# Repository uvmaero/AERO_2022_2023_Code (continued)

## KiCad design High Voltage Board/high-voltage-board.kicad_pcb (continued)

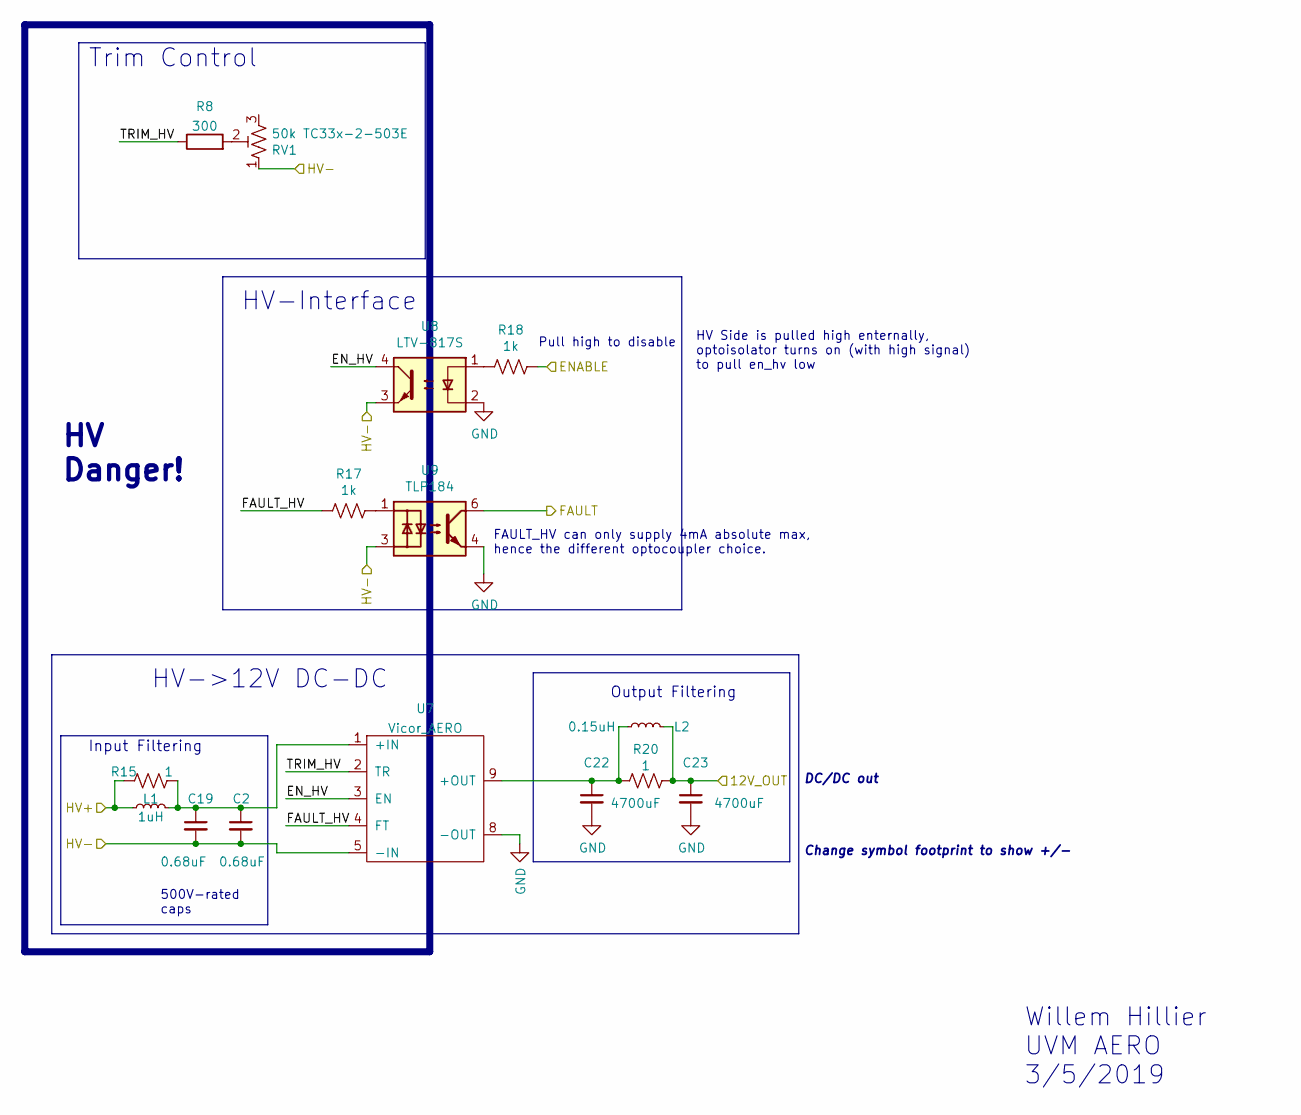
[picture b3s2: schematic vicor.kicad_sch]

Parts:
C2, C19: 0.68uF; C_Rect_L18.0mm_W8.0mm_P15.00mm_FKS3_FKP3
C22, C23: 4700uF; C_Radial_D18.0mm_H35.5mm_P7.50mm
L1: 1uH; L_1008_2520Metric_Pad1.43x2.20mm_HandSolder
L2: 0.15uH; L_0805_2012Metric_Pad1.15x1.40mm_HandSolder
R8: 300; R_0603_1608Metric_Pad0.98x0.95mm_HandSolder
R15, R20: 1; R_2512_6332Metric_Pad1.40x3.35mm_HandSolder
R17, R18: 1k; R_0603_1608Metric_Pad0.98x0.95mm_HandSolder
RV1: 50k TC33x-2-503E; Potentiometer_Bourns_TC33X_Vertical
U7: Vicor_AERO; vicor-socket-no-cutouts
U8: LTV-817S; SMDIP-4_W9.53mm_Clearance8mm
U9: TLP184; MFSOP6-4_4.4x3.6mm_P1.27mm

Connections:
/DCDC_OUT: C23.1, L2.2, R20.1; also elsewhere on the board
/DC_DC_EN: R18.1; also elsewhere on the board
/DC_DC_FAULT: U9.6; also elsewhere on the board
/vicor/EN_HV: U7.3 (EN), U8.4
/vicor/FAULT_HV: R17.2, U7.4 (FT)
/vicor/HV+: L1.1, R15.2; also elsewhere on the board
/vicor/TRIM_HV: R8.1, U7.2 (TR)
GND: C22.2, C23.2, U7.8 (-OUT), U8.2, U9.4; also elsewhere on the board
HV-: C2.2, C19.2, RV1.1, U7.5 (-IN), U8.3, U9.3; also elsewhere on the board
unnamed: C2.1, C19.1, L1.2, R15.1, U7.1 (+IN)
unnamed: C22.1, L2.1, R20.2, U7.9 (+OUT)
unnamed: R8.2, RV1.2
unnamed: R17.1, U9.1
unnamed: R18.2, U8.1

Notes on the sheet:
DC/DC out
Output Filtering
500V-rated caps
Willem Hillier UVM AERO 3/5/2019
Input Filtering
Trim Control
HV-Interface
Change symbol footprint to show +/-
Pull high to disable
HV->12V DC-DC
HV Side is pulled high enternally, optoisolator turns on (with high signal) to pull en_hv low
HV Danger!
FAULT_HV can only supply 4mA absolute max, hence the different optocoupler choice.

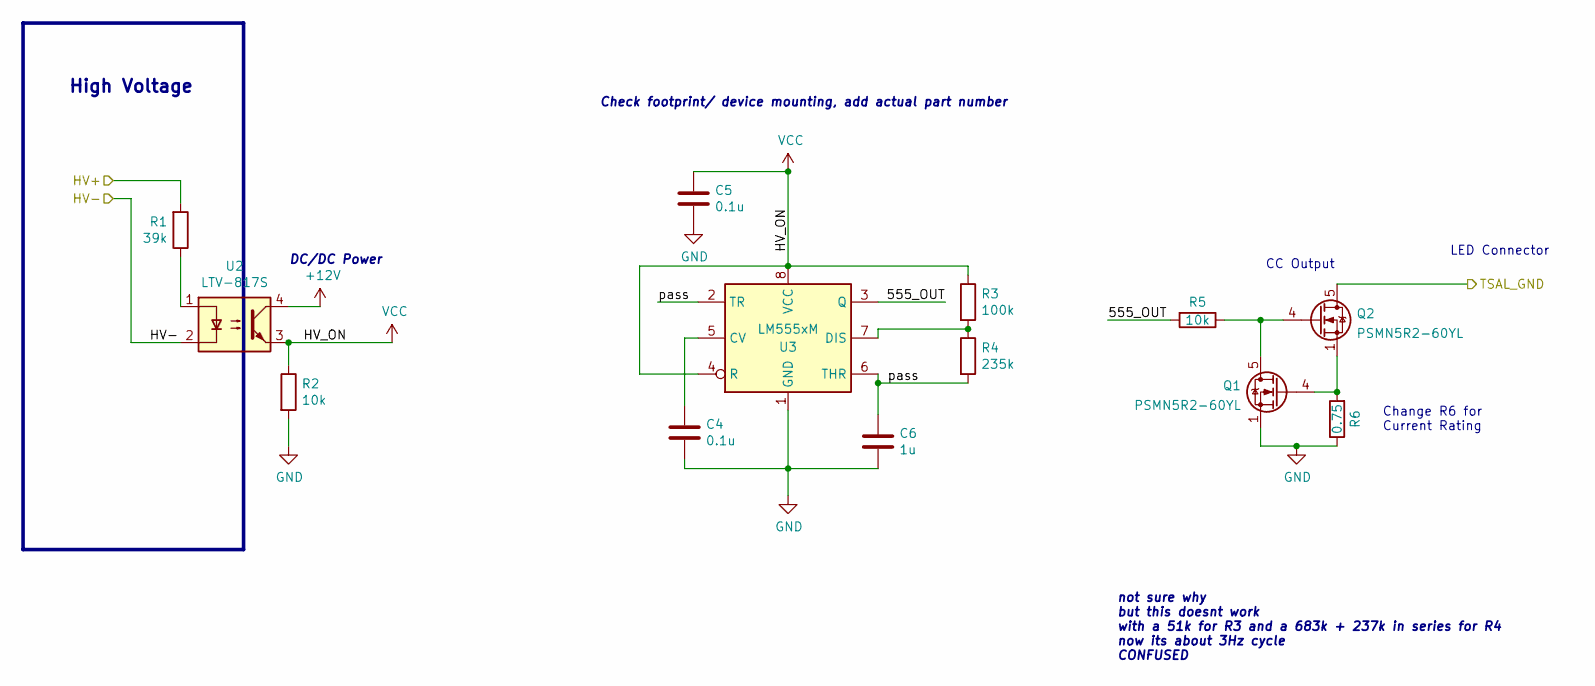
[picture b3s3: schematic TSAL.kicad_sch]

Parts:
C4, C5: 0.1u; C_0603_1608Metric_Pad1.08x0.95mm_HandSolder
C6: 1u; C_0603_1608Metric_Pad1.08x0.95mm_HandSolder
Q1, Q2: PSMN5R2-60YL; LFPAK56
R1: 39k; R_Axial_DIN0411_L9.9mm_D3.6mm_P25.40mm_Horizontal
R2, R5: 10k; R_0603_1608Metric_Pad0.98x0.95mm_HandSolder
R3: 100k; R_0603_1608Metric_Pad0.98x0.95mm_HandSolder
R4: 235k; R_0603_1608Metric_Pad0.98x0.95mm_HandSolder
R6: 0.75; R_2512_6332Metric_Pad1.40x3.35mm_HandSolder
U2: LTV-817S; SMDIP-4_W9.53mm_Clearance8mm
U3: LM555xM; SOIC-8_3.9x4.9mm_P1.27mm

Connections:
+12V: U2.4; also elsewhere on the board
/TSAL/555_OUT: R5.2, U3.3 (Q)
/TSAL/HV+: R1.2; also elsewhere on the board
/TSAL/pass: C6.1, R4.2, U3.2 (TR), U3.6 (THR)
/TSAL_GND: Q2.5 (D); also elsewhere on the board
GND: C4.2, C5.2, C6.2, Q1.1 (S), Q1.2 (S), Q1.3 (S), R2.2, R6.1, U3.1 (GND); also elsewhere on the board
HV-: U2.2; also elsewhere on the board
unnamed: C4.1, U3.5 (CV)
unnamed: Q1.4 (G), Q2.1 (S), Q2.2 (S), Q2.3 (S), R6.2
unnamed: Q1.5 (D), Q2.4 (G), R5.1
unnamed: R1.1, U2.1
unnamed: R3.2, R4.1, U3.7 (DIS)
VCC: C5.1, R2.1, R3.1, U2.3, U3.4 (R), U3.8 (VCC)

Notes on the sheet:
Check footprint/ device mounting, add actual part number
DC/DC Power
Change R6 for Current Rating
CC Output
LED Connector
High Voltage
not sure why but this doesnt work with a 51k for R3 and a 683k + 237k in series for R4 now its about 3Hz cycle CONFUSED

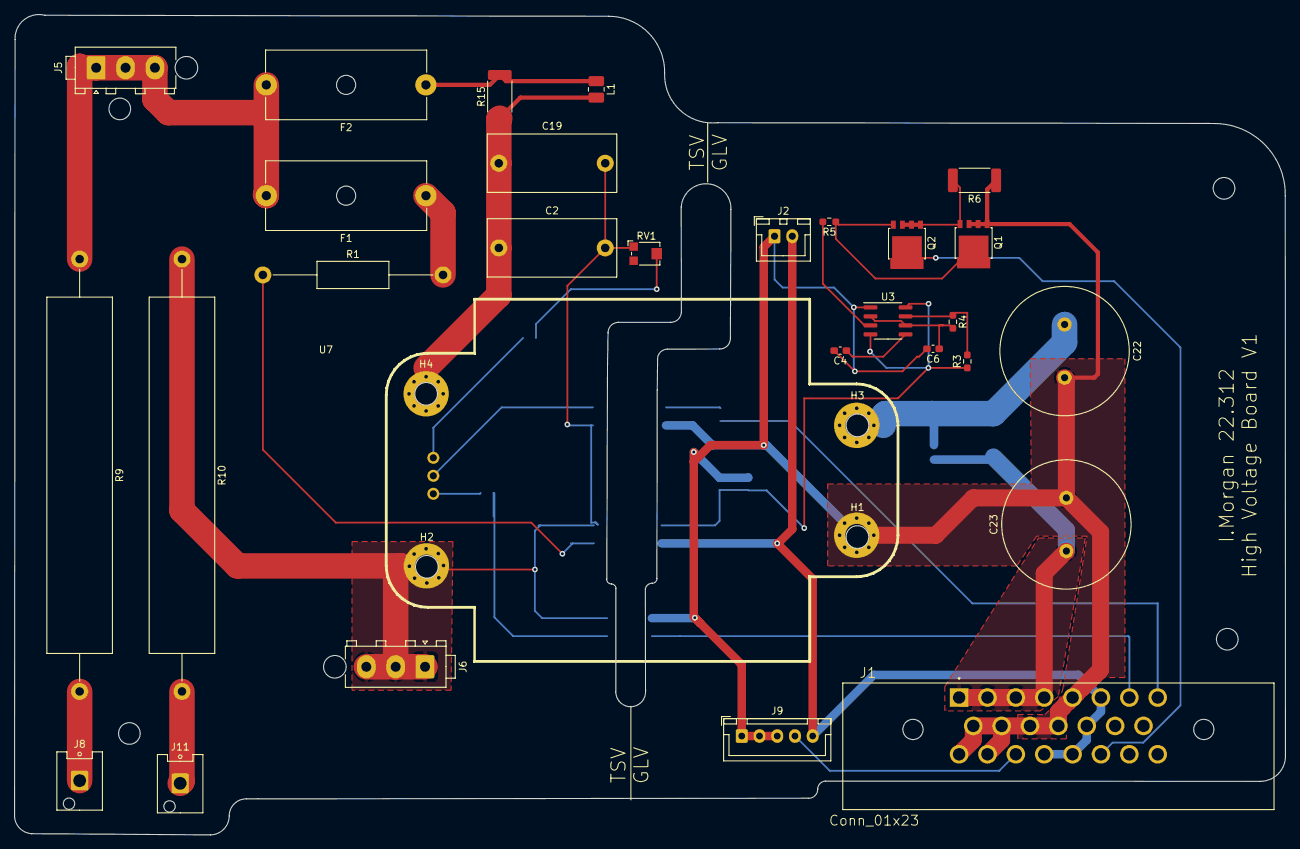
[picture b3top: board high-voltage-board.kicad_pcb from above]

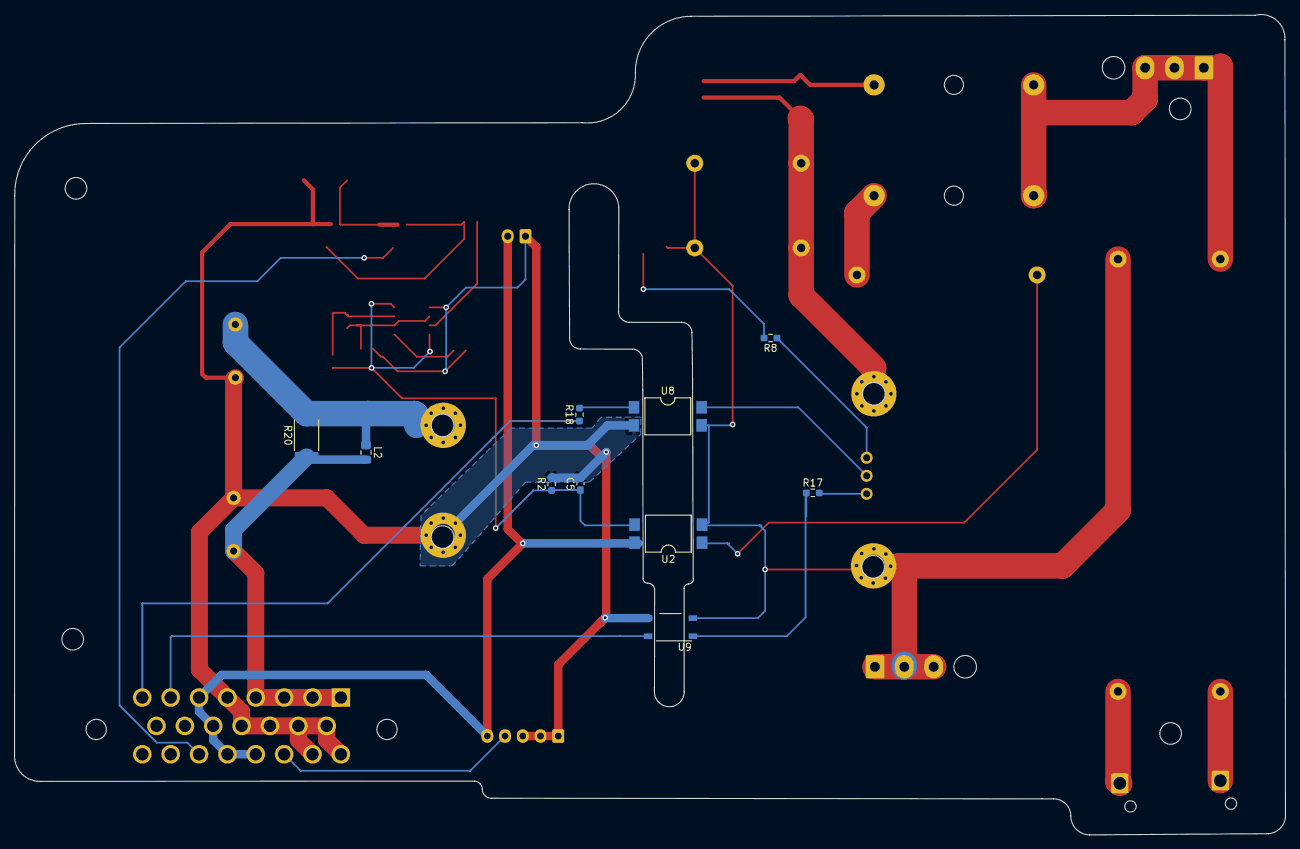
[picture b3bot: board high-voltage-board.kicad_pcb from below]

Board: 2 copper layers, 179.2 x 115.7 mm, 43 parts (10 on the bottom side), 29 nets.

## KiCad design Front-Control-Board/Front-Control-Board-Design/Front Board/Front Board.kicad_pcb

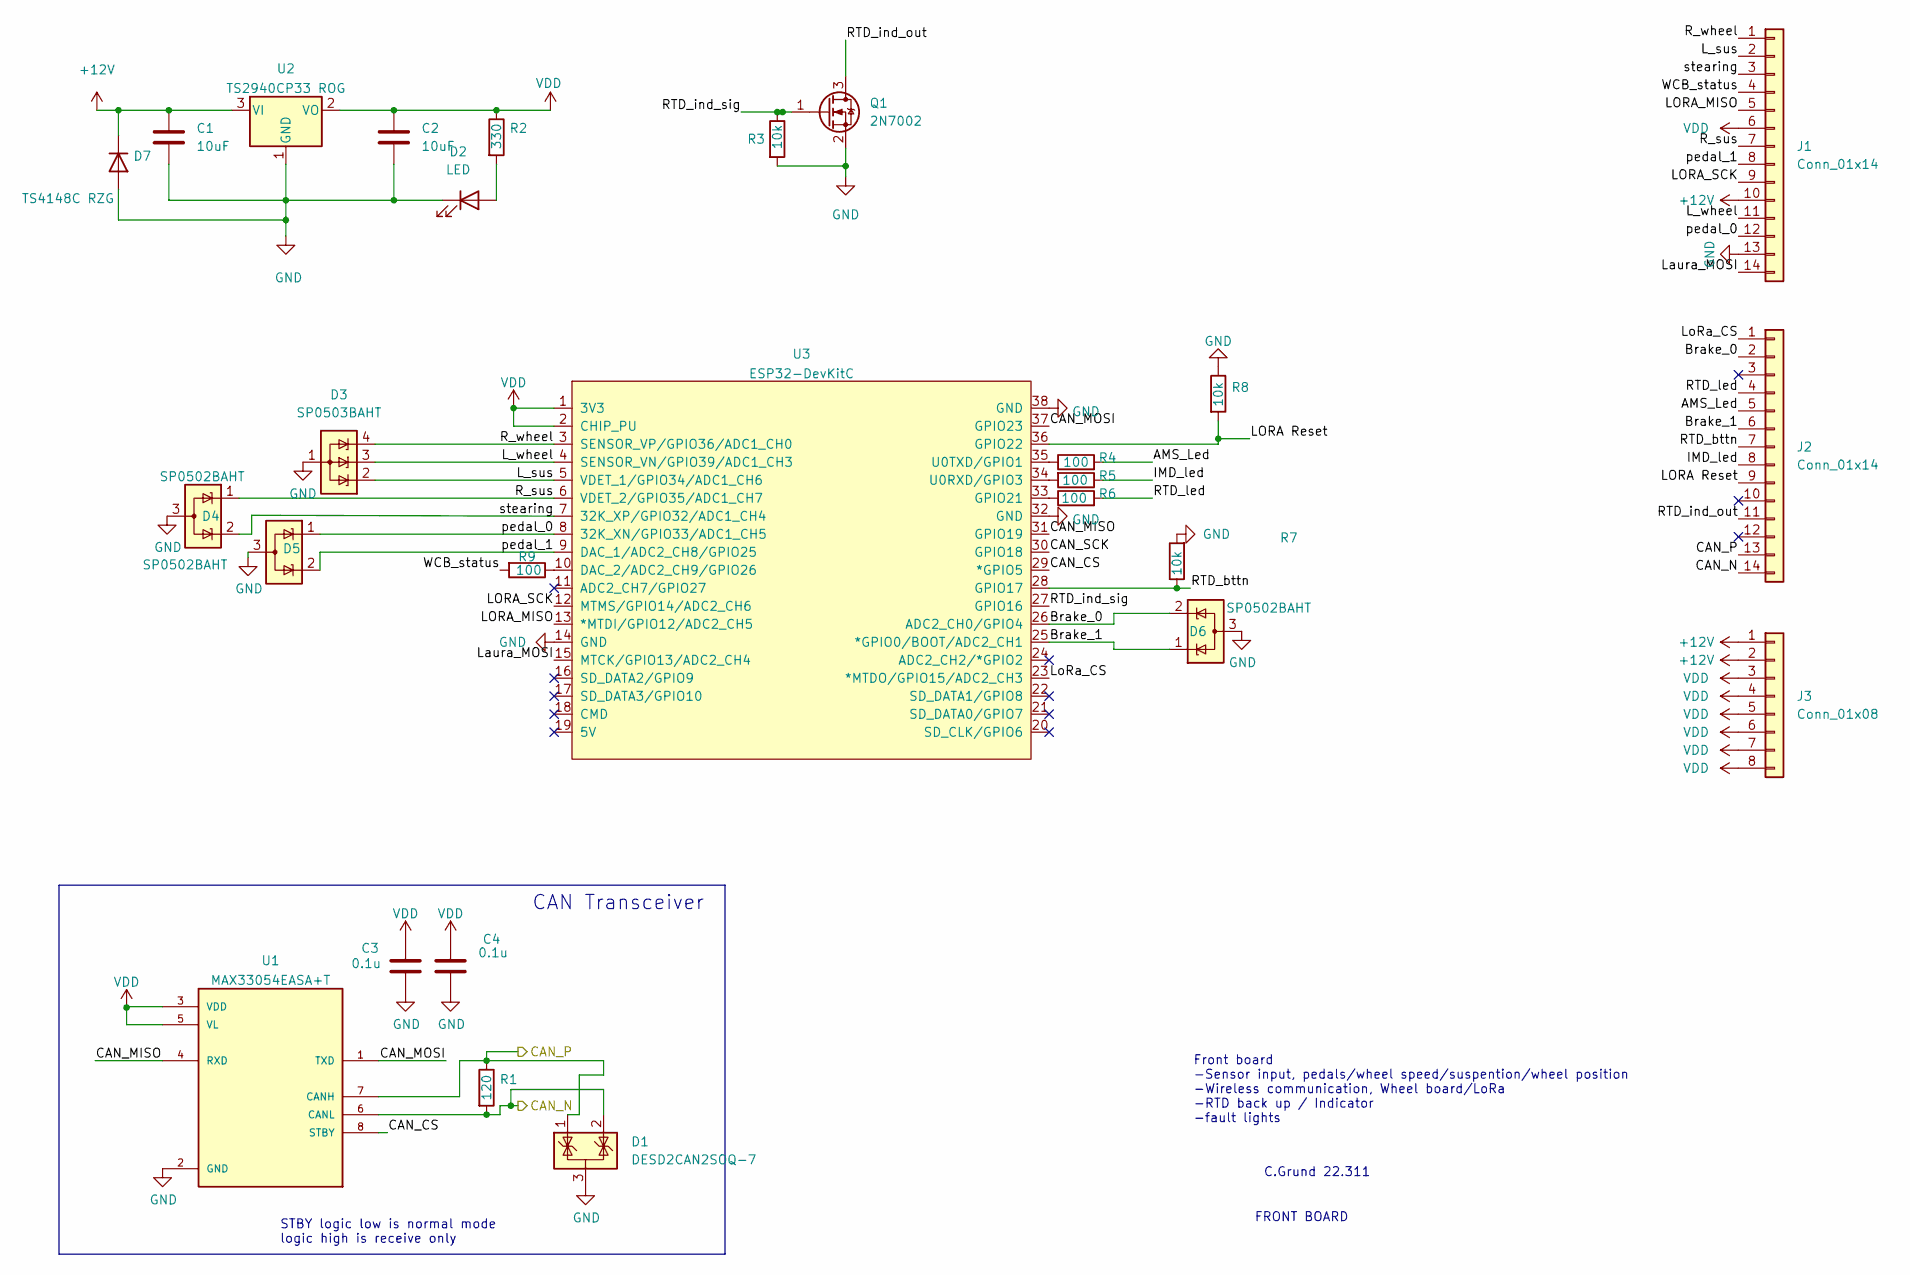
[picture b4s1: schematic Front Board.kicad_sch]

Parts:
C1, C2: 10uF; C_0603_1608Metric_Pad1.08x0.95mm_HandSolder
C3, C4: 0.1u; C_0603_1608Metric_Pad1.08x0.95mm_HandSolder
D1: DESD2CAN2SOQ-7; SOT-23
D2: LED; LED_0603_1608Metric_Pad1.05x0.95mm_HandSolder
D3: SP0503BAHT; SOT-143
D4, D5, D6: SP0502BAHT; SOT-23
D7: TS4148C RZG; D_0603_1608Metric_Pad1.05x0.95mm_HandSolder
J1, J2: Conn_01x14; TE_1-776266-1_14pin_Horizontal
J3: Conn_01x08; TE_1-776280-1_8pin_Horizontal
Q1: 2N7002; SOT-23
R1: 120; R_0603_1608Metric_Pad0.98x0.95mm_HandSolder
R2: 330; R_0603_1608Metric_Pad0.98x0.95mm_HandSolder
R3, R7, R8: 10k; R_0603_1608Metric_Pad0.98x0.95mm_HandSolder
R4, R5, R6, R9: 100; R_0603_1608Metric_Pad0.98x0.95mm_HandSolder
U1: MAX33054EASA+T; SOIC127P600X175-8N
U2: TS2940CP33 ROG; TO-252-2
U3: ESP32-DevKitC

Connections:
+12V: C1.1, D7.1 (K), J1.10, J3.1, J3.2, U2.3 (VI)
/AMS_Led: J2.5, R4.2
/Brake_0: D6.2 (K), J2.2, U3.26 (ADC2_CH0/GPIO4)
/Brake_1: D6.1 (K), J2.6, U3.25 (*GPIO0/BOOT/ADC2_CH1)
/CAN_CS: U1.8 (STBY), U3.29 (*GPIO5)
/CAN_MISO: U1.4 (RXD), U3.31 (GPIO19)
/CAN_MOSI: U1.1 (TXD), U3.37 (GPIO23)
/CAN_N: D1.2 (K), J2.14, R1.2, U1.6 (CANL)
/CAN_P: D1.1 (K), J2.13, R1.1, U1.7 (CANH)
/CAN_SCK: U3.30 (GPIO18)
/IMD_led: J2.8, R5.1
/LORA Reset: J2.9, R8.2, U3.36 (GPIO22)
/LORA_MISO: J1.5, U3.13 (*MTDI/GPIO12/ADC2_CH5)
/LORA_SCK: J1.9, U3.12 (MTMS/GPIO14/ADC2_CH6)
/L_sus: D3.2 (K), J1.2, U3.5 (VDET_1/GPIO34/ADC1_CH6)
/L_wheel: D3.3 (K), J1.11, U3.4 (SENSOR_VN/GPIO39/ADC1_CH3)
/Laura_MOSI: J1.14, U3.15 (MTCK/GPIO13/ADC2_CH4)
/LoRa_CS: J2.1, U3.23 (*MTDO/GPIO15/ADC2_CH3)
/RTD_bttn: J2.7, R7.1, U3.28 (GPIO17)
/RTD_ind_out: J2.11, Q1.3 (D)
/RTD_ind_sig: Q1.1 (G), R3.1, U3.27 (GPIO16)
/RTD_led: J2.4, R6.2
/R_sus: D4.1 (K), J1.7, U3.6 (VDET_2/GPIO35/ADC1_CH7)
/R_wheel: D3.4 (K), J1.1, U3.3 (SENSOR_VP/GPIO36/ADC1_CH0)
/WCB_status: J1.4, R9.2
/pedal_0: D5.1 (K), J1.12, U3.8 (32K_XN/GPIO33/ADC1_CH5)
/pedal_1: D5.2 (K), J1.8, U3.9 (DAC_1/ADC2_CH8/GPIO25)
/stearing: D4.2 (K), J1.3, U3.7 (32K_XP/GPIO32/ADC1_CH4)
GND: C1.2, C2.2, C3.2, C4.2, D1.3 (A), D2.1 (K), D3.1 (A), D4.3 (A), D5.3 (A), D6.3 (A), D7.2 (A), J1.13, Q1.2 (S), R3.2, R7.2, R8.1, U1.2 (GND), U2.1 (GND), U3.14 (GND), U3.32 (GND), U3.38 (GND)
unnamed: D2.2 (A), R2.2
unnamed: R4.1, U3.35 (U0TXD/GPIO1)
unnamed: R5.2, U3.34 (U0RXD/GPIO3)
unnamed: R6.1, U3.33 (GPIO21)
unnamed: R9.1, U3.10 (DAC_2/ADC2_CH9/GPIO26)
VDD: C2.1, C3.1, C4.1, J1.6, J3.3, J3.4, J3.5, J3.6, J3.7, J3.8, R2.1, U1.3 (VDD), U1.5 (VL), U2.2 (VO), U3.1 (3V3), U3.2 (CHIP_PU)

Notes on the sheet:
CAN Transceiver
FRONT BOARD
C.Grund 22.311
Front board -Sensor input, pedals/wheel speed/suspention/wheel position -Wireless communication, Wheel board/LoRa -RTD back up / Indicator -fault lights
STBY logic low is normal mode logic high is receive only

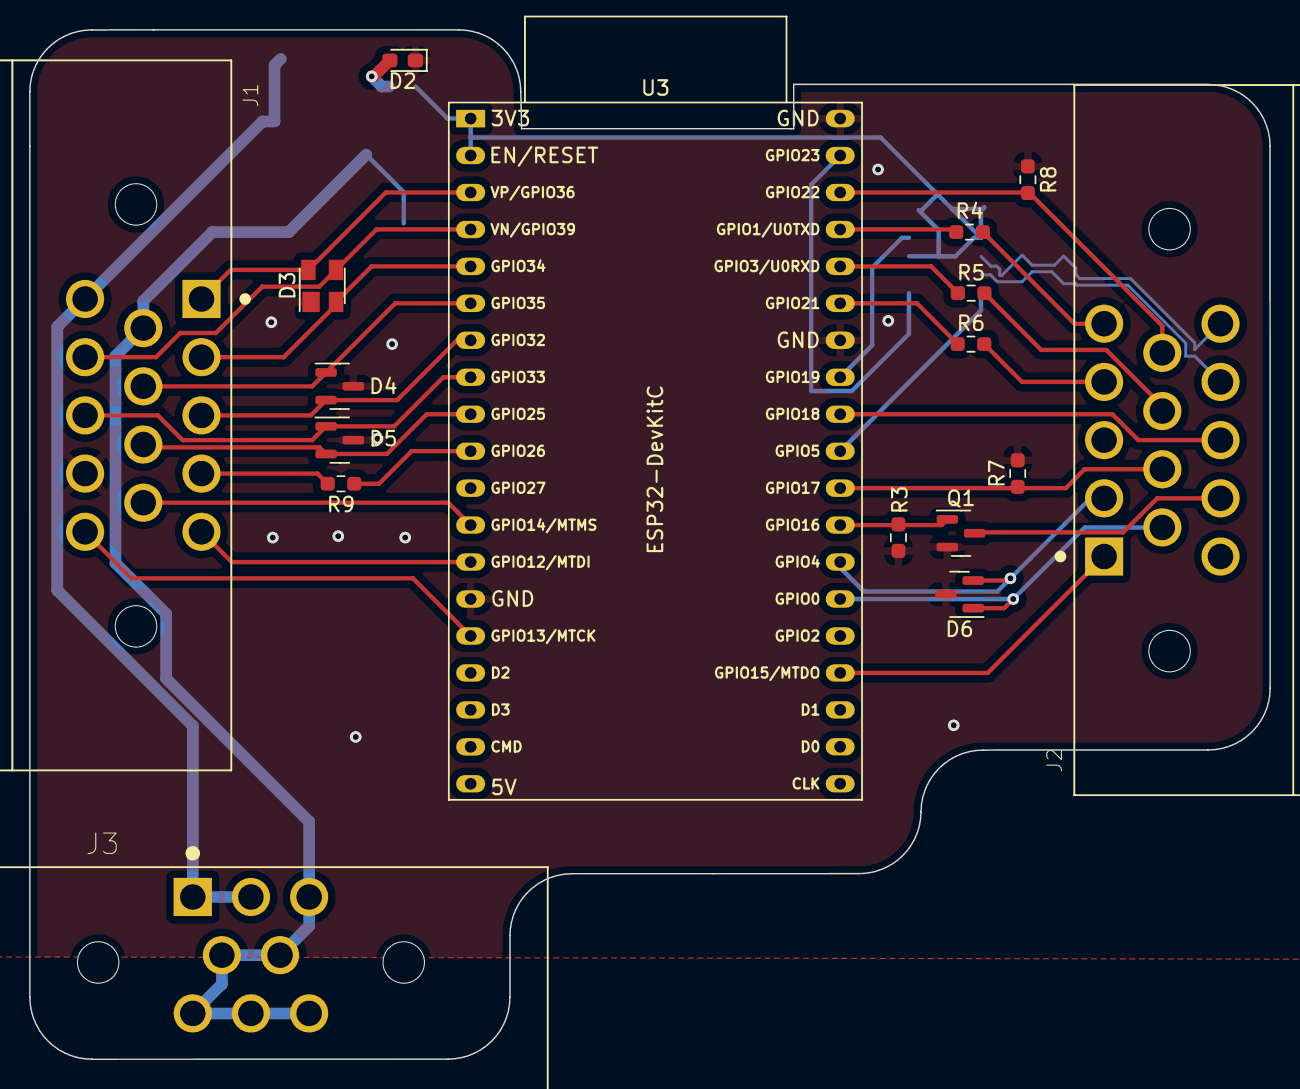
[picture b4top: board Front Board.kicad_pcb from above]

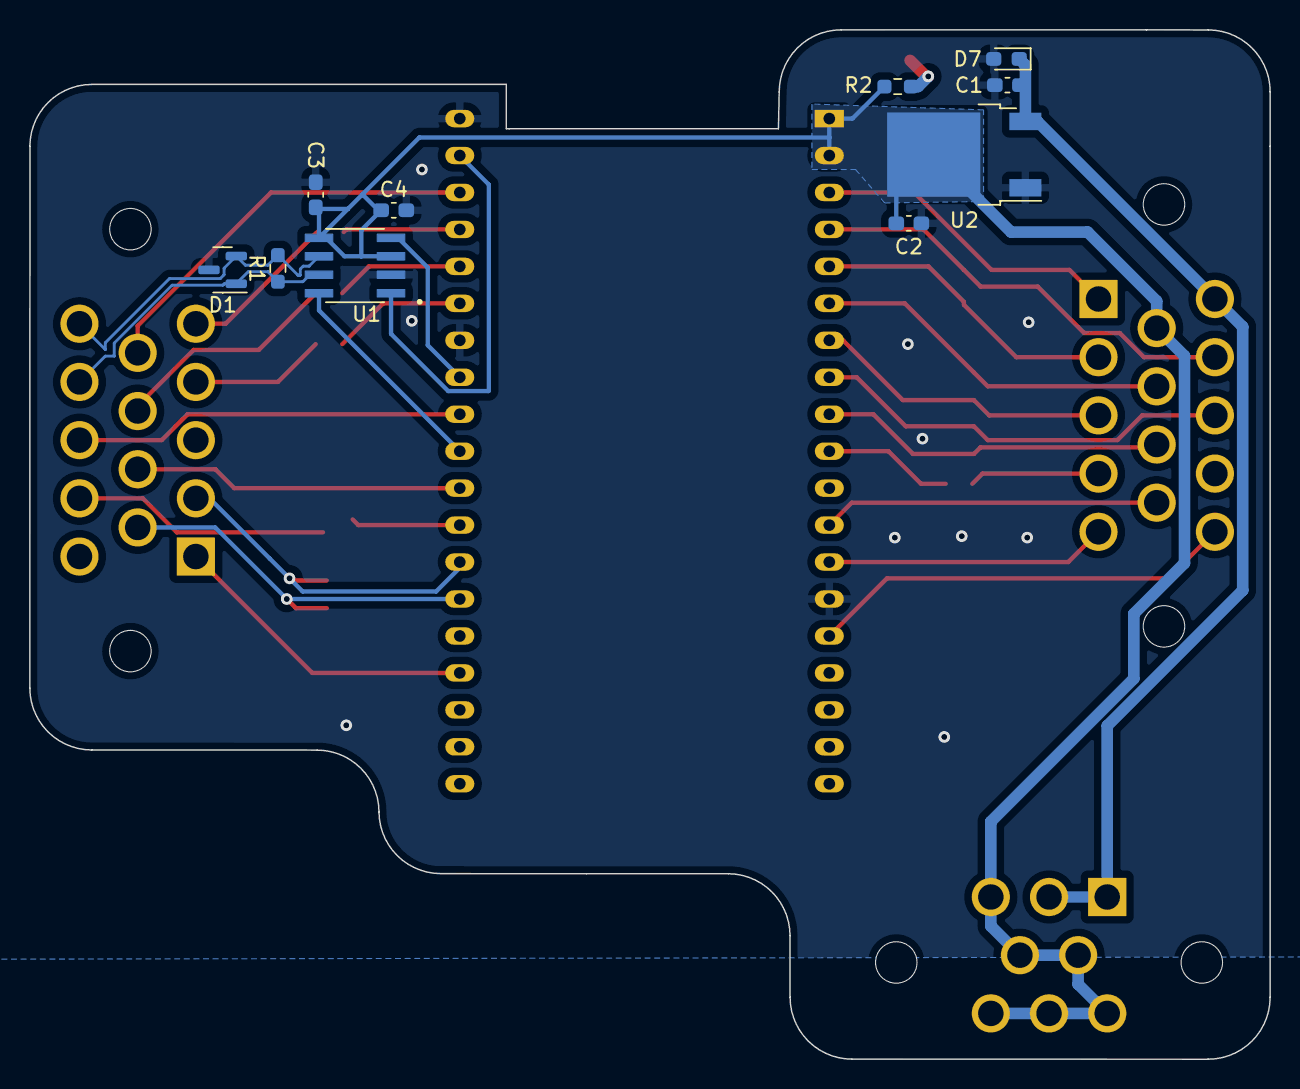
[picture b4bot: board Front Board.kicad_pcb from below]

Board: 2 copper layers, 85.2 x 70.7 mm, 27 parts (10 on the bottom side), 34 nets.

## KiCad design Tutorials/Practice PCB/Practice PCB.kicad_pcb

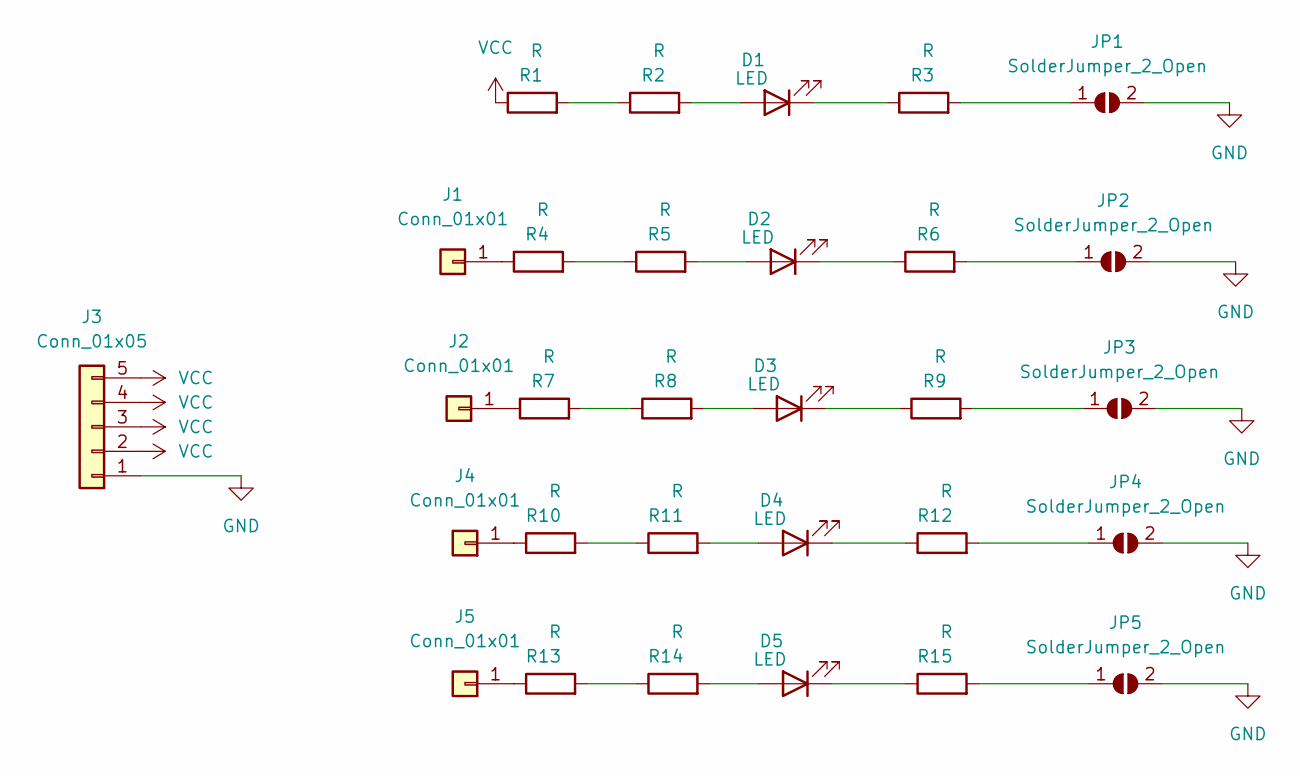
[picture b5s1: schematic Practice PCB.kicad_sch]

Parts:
D1, D2, D3, D4, D5: LED; LED_0603_1608Metric_Pad1.05x0.95mm_HandSolder
J1, J2, J4, J5: Conn_01x01; PinSocket_1x01_P2.00mm_Vertical
J3: Conn_01x05; SolderWire-1.5sqmm_1x05_P6mm_D1.7mm_OD3mm
JP1, JP3, JP5: SolderJumper_2_Open; SolderJumper-2_P1.3mm_Open_RoundedPad1.0x1.5mm
JP2, JP4: SolderJumper_2_Open; SolderJumper-2_P1.3mm_Open_Pad1.0x1.5mm
R1, R4, R7, R10, R13: R; R_Axial_DIN0411_L9.9mm_D3.6mm_P7.62mm_Vertical
R2, R5, R8, R11, R14: R; R_Axial_DIN0411_L9.9mm_D3.6mm_P12.70mm_Horizontal
R3, R6, R9, R12, R15: R; R_0603_1608Metric_Pad0.98x0.95mm_HandSolder

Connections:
GND: J3.1, JP1.2 (B), JP2.2 (B), JP3.2 (B), JP4.2 (B), JP5.2 (B)
unnamed: D1.1 (K), R3.1
unnamed: D1.2 (A), R2.2
unnamed: D2.1 (K), R6.1
unnamed: D2.2 (A), R5.2
unnamed: D3.1 (K), R9.1
unnamed: D3.2 (A), R8.2
unnamed: D4.1 (K), R12.1
unnamed: D4.2 (A), R11.2
unnamed: D5.1 (K), R15.1
unnamed: D5.2 (A), R14.2
unnamed: J1.1, R4.1
unnamed: J2.1, R7.1
unnamed: J4.1, R10.1
unnamed: J5.1, R13.1
unnamed: JP1.1 (A), R3.2
unnamed: JP2.1 (A), R6.2
unnamed: JP3.1 (A), R9.2
unnamed: JP4.1 (A), R12.2
unnamed: JP5.1 (A), R15.2
unnamed: R1.2, R2.1
unnamed: R4.2, R5.1
unnamed: R7.2, R8.1
unnamed: R10.2, R11.1
unnamed: R13.2, R14.1
VCC: J3.2, J3.3, J3.4, J3.5, R1.1

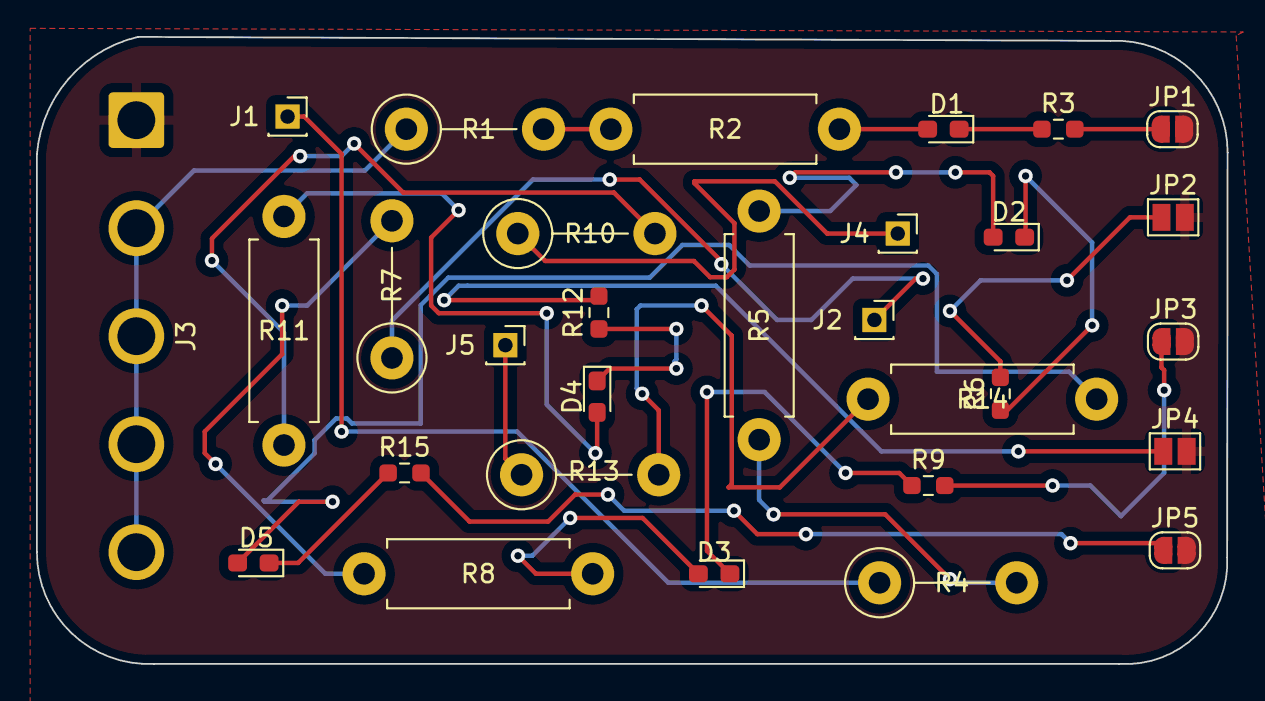
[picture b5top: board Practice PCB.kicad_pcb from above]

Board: 2 copper layers, 66.2 x 34.8 mm, 30 parts (0 on the bottom side), 26 nets.

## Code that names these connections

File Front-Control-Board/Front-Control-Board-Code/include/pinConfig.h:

/**
 * @file pinConfig.h
 * @author dominic gasperini 
 * @brief this file holds the pin layout for the board I/O
 * @version 0.1
 * @date 2022-07-27
 * 
 * @copyright Copyright (c) 2022
 * 
 */


// includes
#include <soc/adc_channel.h>


/*
===========================================================
                    Power Configuration
===========================================================
*/

esp_pm_config_esp32_t power_configuration {
    .max_freq_mhz = 240,   
    .min_freq_mhz = 240,
    .light_sleep_enable = false,
};


/*
===========================================================
                    ESP-NOW Definitions
===========================================================
*/


uint8_t wcbAddress[] = {0xC4, 0xDE, 0xE2, 0xC0, 0x75, 0x80};
uint8_t rcbAddress[] = {0xC4, 0xDE, 0xE2, 0xC0, 0x75, 0x81};
uint8_t deviceAddress[] = {0x1a, 0x1a, 0x1a, 0x1a, 0x1a, 0x1a};


/*
===========================================================
                    Pin Definitions
===========================================================
*/


// Sensors
#define WHEEL_SPEED_FR_SENSOR               ADC1_GPIO32_CHANNEL
#define WHEEL_SPEED_FL_SENSOR               ADC1_GPIO32_CHANNEL

#define WHEEL_HEIGHT_FR_SENSOR              ADC1_GPIO32_CHANNEL
#define WHEEL_HEIGHT_FL_SENSOR              ADC1_GPIO32_CHANNEL

#define STEERING_WHEEL_POT                  ADC1_GPIO32_CHANNEL

#define PEDAL_0_PIN                         ADC1_GPIO32_CHANNEL // use these things to config pins based on gpio #
#define PEDAL_1_PIN                         ADC1_GPIO32_CHANNEL
#define BRAKE_0_PIN                         ADC1_GPIO32_CHANNEL
#define BRAKE_1_PIN                         ADC1_GPIO32_CHANNEL

// Inputs
#define CAN_CS_PIN                          18
#define CAN_MESSAGE_INTERRUPT_PIN           15   
#define CAN_TX_PIN                          21
#define CAN_RX_PIN                          22

// Outputs
#define WCB_CONNECTION_LED                  26
#define BUZZER_PIN                          12
#define ARDAN_SS_PIN                        10
#define ARDAN_RST_PIN                       11
#define ARDAN_DIO_PIN                       14

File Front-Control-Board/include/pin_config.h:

/**
 * @file pinConfig.h
 * @author dominic gasperini 
 * @brief this file holds the pin layout for the board I/O
 * @version 1.0
 * @date 2023-03-22
 * 
 * @copyright Copyright (c) 2022
 * 
 */


// includes
#include <esp_pm.h>

/*
===========================================================
                    Power Configuration
===========================================================
*/

esp_pm_config_esp32_t power_configuration {
    .max_freq_mhz = 240,   
    .min_freq_mhz = 240,
    .light_sleep_enable = false,
};


/*
===========================================================
                    Pin Definitions
===========================================================
*/


// Sensors
#define WHEEL_SPEED_FR_SENSOR               36
#define WHEEL_SPEED_FL_SENSOR               39

#define WHEEL_HEIGHT_FR_SENSOR              34
#define WHEEL_HEIGHT_FL_SENSOR              35

#define STEERING_WHEEL_POT                  32

#define PEDAL_0_PIN                         33
#define PEDAL_1_PIN                         25
#define BRAKE_PIN                           4

// Inputs
#define RTD_BUTTON_PIN                      17

// CAN
#define CAN_RX_PIN                          19
#define CAN_TX_PIN                          23
#define CAN_ENABLE_PIN                      5

// Outputs
#define RTD_LED_PIN                         21
#define WCB_CONNECTION_LED                  26

#define BMS_LED_PIN                         1
#define IMD_LED_PIN                         3

#define BUZZER_PIN                          16

#define ARDAN_MISO_PIN                      12
#define ARDAN_MOSI_PIN                      13
#define ARDAN_CS_PIN                        10

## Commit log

2022-07-26 created dash project
2022-07-26 added some general structure
2022-07-27 just chugging along
2022-07-27 some clean up
2022-07-28 did some BLE setup
2022-07-28 took out some ble stuff
2022-07-28 added some stuff for ardan
2022-07-28 did more things
2022-07-28 decreased sensor poll interval
2022-07-28 added serial messages and other small changes
2022-08-04 switched to esp32-wroom-32e real quick
2022-08-04 finished up CAN, ARDAN, & ESP-NOW
2022-08-04 did most of wcb and small changes to fcb
2022-08-04 did some lcd and button interrupts stuff
2022-08-10 added buzzer logic
2022-08-10 fixed some mistakes and added some LCD stuff
2022-08-10 added LED code
2022-08-10 updated timer timings
2022-08-10 fixed bugs and added comments
2022-08-10 adding folders
2022-08-10 creating folders again
2022-08-10 updated text
2022-08-27 added rear control board folder
2022-08-31 added race mode to lcd
2022-08-31 updated lcd lib to RPI display lib
2022-08-31 fixed adc channel 2 and wifi module conflict
2022-08-31 timer for buzzer is now dynamically managed
2022-09-12 Tutorials and front board
2022-09-20 front board update
2022-09-28 added TODO
2022-10-03 Front board finished schematic
2022-10-03 Front board schematic
    and linking to footprint done
2022-10-03 front board with footprint
2022-10-04 Initial board creation
2022-10-10 Colin Push
2022-10-11 Front board first draft
2022-10-17 added ISR on/off calls to ISRs, updated fcb coms
2022-10-17 added function descriptions
2022-10-17 updated struct to make sense
2022-10-17 fixed up car data struct
2022-10-17 spacing
2022-10-17 updated car data struct again
2022-10-18 Added lin reg and more
2022-10-19 Documentation
2022-10-21 created rear control board project!
2022-10-21 vauge layout for rcb code
2022-10-21 updated deps and removed some stuff
2022-10-21 added placeholder file
2022-10-21 added folder structure in documentation
2022-10-21 updated folder names
2022-10-21 Started rework
    Started reworking the board to fit new board type, added a shortcuts sheet txt so I can remember, and did some general clean up.
2022-11-02 updated pins schematic
2022-11-02 pin layout updated needs PCB
2022-11-03 Front board updated just needs traces
2022-11-05 Front Board V1
2022-11-08 Added HVB V1, and re-push of second PACman
2022-11-08 Repush of initial Pacman
2022-11-08 fixed edge cuts
2022-11-09 touch ups
2022-11-11 Re adding work from 11/11/2022
    Un messing up by adding another version from before a push
2022-11-22 pcb Done? check SD
2022-11-28 Pacman 1 Correction+Reload
2022-11-28 Pac2 Cleanup
2022-11-28 DONE!!!!!
2022-11-29 V1 with all Gerbers
2022-11-29 cleaned up
2023-01-25 updated interrupts to have ISR switches
2023-01-25 added some nice debugging features
2023-01-25 added debugging tracking to interrupts
2023-01-25 implemented CAN debugging print
2023-01-25 added print for some clarity
2023-01-25 implemented WCB debug prints
2023-01-25 updated header
2023-01-25 testing changes
2023-01-27 overhauled timers so now they don't suck
2023-01-27 updated setup prints to use esp logging
2023-01-27 removed unused defines
2023-01-27 compressed CAN read and write into single callback
2023-01-27 switched gpio & wifi from arduino to esp32 api
2023-01-27 implemented rtos ;)
2023-01-27 improved task activation
2023-01-27 removed testing code
2023-01-27 updated file header
2023-01-27 added scheduler debugger
2023-01-29 did some organizing and updated to c++11
2023-01-30 did some organizing
2023-01-30 more clean-up
2023-01-30 cranked power
2023-01-30 more clean-up and added mac address update
2023-01-30 even more clean-up
2023-01-30 clean-up
2023-01-30 comments
2023-01-30 first re-write with FreeRTOS
2023-01-30 transfer celan up
2023-01-30 fixed typo
2023-01-30 consistency
2023-01-30 updated esp-now fcb update func
2023-01-30 updated pinConfig with wcb i/o
2023-01-30 updated poll sensors task
2023-01-30 fixed bug
2023-02-01 started implementing custom display driver library
2023-02-01 added functions and updated headers
2023-02-01 update git ignore
2023-02-01 updated git ignore
2023-02-01 added a second git ignore i guess
2023-02-01 wcb debugger feautre and hall effect callback
2023-02-01 implemented gpio for fr & fl hall effects
2023-02-01 more work on gpio & adc config
2023-02-02 removed dead code
2023-02-02 added some stuff for testing wcb esp-now
2023-02-02 testing
2023-02-02 testing again
2023-02-02 updated car data struct
2023-02-02 updated wcb address
2023-02-02 updated esp-now callback
2023-02-06 fixed typos
2023-02-06 typo and potential bug fix
2023-02-06 applied potential bug fix
2023-02-06 gone and done some more bug squashin
2023-02-06 zip zop there go mistakes
2023-02-06 found a potenital overflow oooo spooky
2023-02-06 updated data types
2023-02-08 updated wifi & espnow setup to meet espressif std
2023-02-08 updated setup prints
2023-02-08 added rcb update task
2023-02-08 fixed debug counter typo
2023-02-08 updated tmp rcb address
2023-02-16 updated CAN stuff
2023-02-16 auto gen file &git ig update
2023-02-16 ag again
2023-02-17 updated can pins
2023-02-17 updated wcb led conn pin
2023-02-18 idk how that compiled
2023-02-18 fixed some bugs
2023-02-18 added alert logging
2023-02-18 whatever at this point
2023-02-21 colin
2023-02-21 did the things and now this exists
2023-02-21 compiles now
2023-02-21 removed non-needed code
2023-02-21 added brake light code
2023-02-21 updated car data typo & added pump temp reads
2023-02-21 did more gpio stuff
2023-02-21 updated debugging stuff
2023-02-21 updated data types changes
2023-02-22 started implementing sd stuff
2023-02-23 update can flag
2023-02-24 more sd card work
2023-02-24 formatting
2023-02-24 added sd card tracker file read & update logic
2023-02-24 log file!
2023-02-24 added function header
2023-02-24 removed unused deps
2023-02-24 updated debugger, added wcb update, & filtered incoming fcb data
2023-02-24 fixed technical bug
2023-02-25 implemented precharge state machine
2023-02-25 added comments
2023-02-25 updated car data init
2023-02-25 added rinehart can recieve
2023-02-25 can stuff and gpio stuff
2023-02-25 fixed gpio mostly probably
2023-02-25 added can stuff and fixed some bugs
2023-02-25 faults and such
2023-02-26 removed dumb stuff
2023-02-26 updated filenames and setup some adc stuff
2023-02-26 removed unused stuff
2023-02-26 fixed casting bug
2023-02-27 fixed dependencies & added some GUI elements
2023-02-27 did display stuff
2023-02-28 boot screen!
2023-02-28 did main screen
2023-02-28 removed dumb code
2023-02-28 did electrical screen
2023-02-28 did mechanical screen
2023-02-28 added screen reset things
2023-02-28 setup button interrupts
2023-02-28 did the thiing
2023-02-28 updated stuff
2023-02-28 fixed bugs
2023-02-28 fixed some bugs and now it works
2023-03-01 cranked
2023-03-01 fixed bug and cranked
2023-03-01 added precharge debug
2023-03-06 removed board design stuff
2023-03-06 last board file
2023-03-06 found more hidden board files
2023-03-06 fixed git ignore
2023-03-21 removed non fcb stuff
2023-03-22 updated LoRa library
2023-03-22 v1 we did it
2023-03-27 got pedal calibrated and working
2023-03-28 fixed can stdby mode issue
2023-03-29 idk gpio things
2023-03-31 AHHHHH
2023-03-31 boy oh boy arduino moments are flying
2023-03-31 maybe done for now
2023-04-02 switched back to esp32 CAN library
2023-04-03 updated name and deleted old files
2023-04-03 fixed
2023-04-03 updated logger stuff
2023-04-03 fixed weird gpio bug
2023-04-03 cleaned up CAN debugging
2023-04-03 fixed precharge
2023-04-03 CAN pins and SD stuff
2023-04-03 CAN debug enabled
2023-04-03 updated folder name
2023-04-03 fixed header comment
2023-04-04 improved CAN debugger
2023-04-04 forgot some formatting
2023-04-04 again ^
2023-04-04 can debugging is even better now!
2023-04-04 finishd setting up esp-now
2023-04-04 fixed CAN bug
2023-04-04 fixed bit shifting and improved can debugging
2023-04-04 calibrated pedals
2023-04-04 testing can coms between rcb and fcb
2023-04-04 AHHHHHHHHHHH
2023-04-04 commented stuff out
2023-04-05 lots of epic changes to make the code very cool
2023-04-05 fixed tasks and now then all run nice
2023-04-05 fixed up sd card code
2023-04-05 fixed task timing bug & general clean up
2023-04-05 fixed can timer interval
2023-04-06 sd card maybe working
2023-04-06 can pins were backwards again...
2023-04-06 front board pins correct
2023-04-06 turns out rear was fine
2023-04-10 updated BMS CAN address stuff
2023-04-10 comment
2023-04-10 updated mac address code and some define names
2023-04-15 updated brake code
2023-04-16 added fault led switching
2023-04-16 added rtd check back in
2023-04-16 added another check
2023-04-16 added more pack data
2023-04-17 updated LEDs
2023-04-18 fixed the inverted thing
2023-04-18 added rtd = true
2023-04-18 fixing up precharge
2023-04-19 added input pullup
2023-04-19 debugging
2023-04-19 optimized sensor reads and updated names
2023-04-19 moved can inits around
2023-04-19 formatting again
2023-04-20 epic changes
2023-04-20 gave leds back
2023-04-23 updated things
2023-04-23 updated bms fault
2023-04-23 fixed comments and bms fault polarity
2023-04-24 ready to drive!!!!!!!
2023-04-25 added custom throttle response for each drive mode
2023-04-26 replaced magic with def
2023-04-26 upped pedal deadband
2023-04-26 oops they were backwards
2023-04-27 increased brake threshold
2023-04-27 long rangeeee
2023-04-27 removed commented out code
2023-04-27 increased ardan update interval
2023-04-30 brake light pin update
2023-04-30 increased brake light threshold
2023-04-30 updated task priorities and timings
2023-04-30 disabled debugging
2023-04-30 disabled brake check
2023-05-01 fixed torque response
2023-05-02 fixed pedal calibration
2023-05-03 updated timings
2023-05-03 drive ready
2023-05-05 fixes to orion can reads
